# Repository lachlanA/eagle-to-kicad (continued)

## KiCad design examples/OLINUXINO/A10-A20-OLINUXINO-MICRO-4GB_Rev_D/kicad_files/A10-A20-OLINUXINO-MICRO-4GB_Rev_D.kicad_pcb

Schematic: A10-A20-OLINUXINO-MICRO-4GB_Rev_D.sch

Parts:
1.2V_CPU233, 1.2V_INT233, 1.5V233, 2.5V233, 3.0VA233, 3.3V233, 5VEXT233: TESTPADTESTPAD_40-ROUND; GOGO_TESTPAD_40-ROUND
5V_E233: Open; JUMPER_SJ_1_SMALLER
5V_E_SATA233: JUMPER_SJ_1_SMALLER
5V_PWR233: NA(DW02S); PENKO_DW02S
5V_SATA_PWR233: DW02S; PENKO_DW02S
+5V233: TESTPADTESTPAD_40-ROUND; GOGO_TESTPAD_40-ROUND
BAT233: TESTPADTESTPAD_40-ROUND; GOGO_TESTPAD_40-ROUND
C1, C4, C6, C8, C9, C12, C16, C17, C20, C28, C29, C30, C31, C32, C33, C34, C35, C36, C37, C38, C39, C40, C41, C42, C43, C44, C45, C46, C47, C48, C49, C50, C51, C52, C53, C54, C55, C58, C81, C111, C114, C117, C118, C119, C120, C224, C225, C226, C227, C228, C229, C230, C231, C232: 220nF; RCL_C0603_DWS
C2, C3, C5, C7, C10, C11, C14, C15, C18, C19, C21, C22, C23, C24, C25, C26, C27, C57, C59, C60, C61, C62, C68, C69, C70, C77, C78, C79, C80, C82, C83, C84, C85, C86, C87, C106, C134, C139, C155, C169, C175, C184, C189, C191: 220nF; RCL_C0402_TI
C13, C56, C64, C67, C76, C101, C103, C104, C105, C109, C115, C133, C138, C157, C168, C173, C186, C190, C193, C194, C197, C198, C199, C204, C205, C206, C207, C209, C210, C211, C212, C219, C220: 22uF/6.3V; RCL_C0603_DWS
C63, C65, C66, C74, C75, C88, C89, C90, C92, C93, C94, C95, C96, C122, C124, C125, C130, C137, C161, C170, C171, C176, C203, C216, C221: 100nF; RCL_C0603_DWS
C71, C181, C183, C185, C188: NA; RCL_C0603_DWS
C72, C73, C99, C100: 33pF; RCL_C0603_DWS
C91, C110, C146, C150, C167, C174: 1uF; RCL_C0603_DWS
C97, C98: 10pF; RCL_C0603_DWS
C102: 100nF; RCL_C0402_TI
C107, C108: NC; RCL_C0402_TI
C112, C113, C121, C128, C136, C145, C147, C148, C149, C151, C152, C156, C158, C159, C162, C164, C166, C172, C177, C178, C179, C180, C187: 10uF/6.3V; RCL_C0603_DWS
C116, C144: NA(2.2uF); RCL_C0603_DWS
C123, C126, C135: 100uF/16V/LOWESR/105C/6.3x11mm_RM2.5; RCL_E2_5-6_3
C127, C129, C131, C132, C160, C165, C182, C218: 1nF; RCL_C0603_DWS
C140, C141, C142, C143, C200: 10nF; RCL_C0402_TI
C153, C154: NA; RCL_C0402_TI
C163, C201: 3.3nF; RCL_C0603_DWS
C192, C196: 470nF; RCL_C0603_DWS
C195, C208: 22pF; RCL_C0603_DWS
C202: 470uF/25V/LOWESR/105C; RCL_E5-10_5
C213, C214, C215: NA(22uF/6.3V); RCL_C0603_DWS
CHGLED233: LED/YELLOW/0603; DOUBLE-SIDE_LED-0603
D1, D3: 1N5819(S4SOD-123); GOGO_SOD-123
D4: 1N5822/SS34/SMA; GOGO_MLL-41
D5: SMBJ16A; OLIMEX_DISCRET_DO214AA
D6: 1N5822/SS34/SMA; SEMICON-SMD-IPC_MELF-MLL41
ENTER233: SIDE_WTCM-TR(3X4); GOGO_SW_TAKT3X4
ESC233: SIDE_WTCM-TR(3X4); GOGO_SW_TAKT3X4
FET1, FET4: IRLML6402; PENKO_SOT23
FET2, FET3: BSS138; PENKO_SOT23
FUSE1: FSMD035; GOGO_1206
GND233: TESTPADTESTPAD_40-ROUND; GOGO_TESTPAD_40-ROUND
GND_PIN233: TESTPAD3; GOGO_TEST_PAD40_70_SQUARE
GPIO-1, GPIO-2, GPIO-3: GBH-254-SMT-40; CON-HARTING-ML_ML40-MALE(GBH-254-SMT-40)
HDMI233: HDMI-SWM-19; OLIMEX_CONNECTORS_HDMI-SWM-19
HEADPHONES233: PJ-W47S-05D2-LF_V2; GOGO_PJ-W47S-05D2-LF_5PIN_V2
HOME233: SIDE_WTCM-TR(3X4); GOGO_SW_TAKT3X4
IPSOUT233: TESTPADTESTPAD_40-ROUND; GOGO_TESTPAD_40-ROUND
L1, L2, L3, L7, L15, L16, L17: FB0805/600R/200mA(201209-601); RCL_L0805_5MIL_DWS
L4, L5: CL470nH/0805/1.76R/250mA; RCL_L0805_5MIL_DWS
L6, L8, L10, L11: FB0805/600R/2A; RCL_L0805_5MIL_DWS
L12, L13, L14, L18, L20, L21: 2.2uH/1.5A/DCR<0.1R/CD32; OLIMEX_DISCRET_CD32
L19: 10uH/3.15A/20%; OLIMEX_DISCRET_8X8MM_3131
LAN233: RJLBC-060TC1_GND_MILLING; OLIMEX_CONNECTORS_RJLBC-060TC1_MILLING
LCD_CON233: GBH-254-SMT-40; CON-HARTING-ML_ML40-MALE(GBH-254-SMT-40)
LED1: LED/GREEN/0603; DOUBLE-SIDE_LED-0603
LIPO_BAT233: DW02R; PENKO_DW02R
MENU233: SIDE_WTCM-TR(3X4); GOGO_SW_TAKT3X4
MIC2: NA(HN1x2); JUMPER_JP1
MIC_IN233: PJ-W47S-05D2-LF_V2; GOGO_PJ-W47S-05D2-LF_5PIN_V2
NAND_E233: Close; JUMPER_SJ_1_SMALLER_CLOSE_10MILS
ODT1: TESTPADTESTPAD_40-ROUND; GOGO_TESTPAD_40-ROUND
PWR233: YDJ-1136; GOGO_PWR_JACK_UNI_MILLING
PWR_BUT233: SIDE_WTCM-TR(3X4); GOGO_SW_TAKT3X4
PWR_LED233: LED/RED/0603; DOUBLE-SIDE_LED-0603
Q1: 4SB25.000F20E15/5x3.2mm/20ppm/20pF; CRYSTAL_HCX-4S
Q2: 32768Hz/6pF; CRYSTAL_TC26H_3_REPAIR_SMD
Q3: 4SB24.000F20E15/5x3.2mm/20ppm/20pF; CRYSTAL_HCX-4S
R1, R2, R4, R6, R8, R20, R37, R39, R57: 2k/1%; RCL_R0603_5MIL_DWS
R3, R31, R51, R53, R60, R62, R63, R66, R68, R71, R72, R74: 1R; RCL_R0603_5MIL_DWS
R5, R23, R25, R49, R50: NA; RCL_R0603_5MIL_DWS
R7, R9, R16: 237R/1%; RCL_R0603_5MIL_DWS
R10, R18, R19, R21, R30, R33, R38, R44, R46, R47, R54, R105, R136, R137: 10k; RCL_R0603_5MIL_DWS
R11, R17, R29, R91: 100k/1%; RCL_R0603_5MIL_DWS
R12, R15: NA; RCL_R0402_TI
R13, R14: NA(2.2k); RCL_R0603_5MIL_DWS
R22, R26: 560R; RCL_R0603_5MIL_DWS
R24, R34, R69, R87: 0R(Board_Mounted); OLIMEX_DISCRET_0603_0R
R27, R28, R40, R52, R79, R84, R95: 47k; RCL_R0603_5MIL_DWS
R32, R65, R70, R73, R75, R76, R81, R82, R83, R85, R93, R94, R120: 2.2k; RCL_R0603_5MIL_DWS
R35: NA(0R); RCL_R0603_5MIL_DWS
R36, R56, R67: 200k/1%; RCL_R0603_5MIL_DWS
R41, R86, R104: 1k/1%; RCL_R0603_5MIL_DWS
R42, R61, R77, R80, R89, R138: 4.99k/1%; RCL_R0603_5MIL_DWS
R43, R103: 51R; RCL_R0603_5MIL_DWS
R45, R48, R55, R100: 13k/1%; RCL_R0603_5MIL_DWS
R58: 100R; RCL_R0603_5MIL_DWS
R59: 0.03R/1%; RCL_R1206_5MIL_WS
R64: 191R/1%; RCL_R0603_5MIL_DWS
R78: 3.32k/1%; RCL_R0603_5MIL_DWS
R88, R97: 8.25k/1%; RCL_R0603_5MIL_DWS
R90, R92: 1.1k/1%; RCL_R0603_5MIL_DWS
R96: 6.81k/1%; RCL_R0603_5MIL_DWS
R98: 10k/1%; RCL_R0603_5MIL_DWS
R99: 11k/1%; RCL_R0603_5MIL_DWS
R101: 16.2k/1%; RCL_R0603_5MIL_DWS
R102: 22.1k/1%; RCL_R0603_5MIL_DWS
R106, R107, R108, R109, R110, R111, R112, R113, R114, R115, R116, R117, R118, R119, R133, R134, R135: 22R; RCL_R0402_TI
R121: NA(10k); RCL_R0603_5MIL_DWS
R122, R123, R124, R125, R126, R127, R128, R129, R130, R131, R132: NA(0R); RCL_R0402_TI
RECOVERY233: SIDE_WTCM-TR(3X4); GOGO_SW_TAKT3X4
RESET233: SIDE_WTCM-TR(3X4); GOGO_SW_TAKT3X4
RM1, RM2, RM3, RM4, RM5, RM6, RM7, RM8, RM16, RM17, RM18, RM19, RM20, RM21: RA0805_(4X0402)_22R; OLIMEX_DISCRET_R_MATRIX_4_0402_25X625
RM9, RM10: RA1206_(4X0603)_4B8_4.7k; OLIMEX_DISCRET_R_MATRIX_4
RM13: RA1206_(4X0603)_4B8_51R; OLIMEX_DISCRET_R_MATRIX_4
RM14, RM15: RA1206_(4X0603)_4B8_100K; OLIMEX_DISCRET_R_MATRIX_4
RM24: RA1206_(4X0603)_4B8_75R; OLIMEX_DISCRET_R_MATRIX_4
RM25: RA1206_(4X0603)_4B8_10k; OLIMEX_DISCRET_R_MATRIX_4
SATA233: SATA-PWA-07; OLIMEX_CONNECTORS_SATA-PWA-07
SCKE1: TESTPADTESTPAD_40-ROUND; GOGO_TESTPAD_40-ROUND
SD/MMC1: MICRO_SD/MMC_CP_NEWTFC-WPAPR-08; OLIMEX_CONNECTORS_TFC-WPAPR-08
SD/MMC2: PSD006A-LT2-BA0; OLIMEX_CONNECTORS_SD_CARD
SEARCH233: SIDE_WTCM-TR(3X4); GOGO_SW_TAKT3X4
T1: BC846B; SEMICON-SMD-IPC_SOT23
U1: A10/A20; OLIMEX_IC_TFBGA441
U2, U3: H5TQ2G63BFR_MEM4G16D3EABG-125; OLIMEX_IC_FBGA96_MEM
U6: AT24C16BN-SH; GOGO_SO-08MN
U7: RTL8201CP; OLIMEX_IC_LQFP48
U8: H27UBG8T2BTR; OLIMEX_IC_TSOP48
U9, U10, U11: SY6280; OLIMEX_IC_SOT23-5
U12: AXP209(QFN48); OLIMEX_IC_QFN48
U13, U15: SY8008C(AA)C; OLIMEX_IC_SOT23-5
U14: MP1482DS; OLIMEX_IC_SOIC8
U16: SY7208(SOT23-6); OLIMEX_IC_SOT23-6
U17, U22, U23: RCLAMP0524P; OLIMEX_IC_SLP2510P8
UART0: HN1X4; PENKO_HN1X4
UEXT1, UEXT2: GBH-254-SMT-10; CON-HARTING-ML_ML10_S
USB_HOST233: USB_TWO_LEVEL; OLIMEX_CONNECTORS_USB_TWO_LEVEL
USB_OTG233: USB-OTG; OLIMEX_CONNECTORS_USB_MINI_9PIN
VGA233: WU06S; DOUBLE-SIDE_CON1.27MM-6-SMALL_ICSP
VOL+233: SIDE_WTCM-TR(3X4); GOGO_SW_TAKT3X4
VOL-233: SIDE_WTCM-TR(3X4); GOGO_SW_TAKT3X4
VPS+233: Open; JUMPER_SJ_1_SMALLER
VPS-233: Open; JUMPER_SJ_1_SMALLER
VP_0, VP_1, VP_2, VP_3, VP_4, VP_5, VP_6, VP_7, VP_9, VP_10, VP_11, VP_12, VP_13, VP_14, VP_15, VP_16, VP_18, VP_19, VP_20, VP_21, VP_22, VP_23, VP_24, VP_25, VP_27, VP_28, VP_29, VP_30, VP_31, VP_32, VP_33, VP_34, VP_36, VP_37, VP_38, VP_39, VP_40, VP_41, VP_42, VP_44, VP_45, VP_46, VP_47, VP_48, VP_49, VP_54, VP_55, VP_56: VPDEV0; VPAD_VPAC0
VP_8, VP_17, VP_26, VP_35: VPDEV1; VPAD_VPAC1
VP_43: VPDEV2; VPAD_VPAC2
VP_50, VP_51, VP_53: VPDEV3; VPAD_VPAC3
VP_52: VPDEV4; VPAD_VPAC4
VR1: AP1231-2.5V(SOT23-5); OLIMEX_DISCRET_SOT-23-5

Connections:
+5V: 5V_E233.2, 5V_E_SATA233.1, 5V_PWR233.1, +5V233.1, C125.1, C128.1, C136.1, C214.2, C215.2, D4.K (C), FET1.2 (S), FET4.2 (S), FUSE1.1, GPIO-1.1, GPIO-2.1, GPIO-3.1, LCD_CON233.1, R37.2, R39.2, R41.1, R104.1, R137.1, U9.5 (IN), U10.5 (IN), U11.5 (IN)
+5V_OTG_PWR: C124.1, L6.1, R17.1, R63.2, U12.31 (VBUS), USB_OTG233.VBUS
+15V: 5VEXT233.1, 5V_E233.1, C204.1, C205.1, D4.A, FET1.1 (G), L19.2, R62.2, R80.2, R81.1, U12.32 (ACIN), U12.33 (ACIN)
+24V: BAT233.1, C150.2, C152.1, C209.2, LIPO_BAT233.1, R59.2, U12.38 (BAT), U12.39 (BAT), U12.42 (BATSENSE)
ADBG: U1.N8 (ADBG)
BA0: RM21.1.2 (2), U2.M2 (BA0), U3.M2 (BA0)
BA1: RM21.4.2 (2), U2.N8 (BA1), U3.N8 (BA1)
BA2: RM21.2.2 (2), U2.M3 (BA2), U3.M3 (BA2)
CASN: RM18.3.2 (2), U2.K3 (#CAS), U3.K3 (#CAS)
CKE: RM20.3.2 (2), U2.K9 (CKE), U3.K9 (CKE)
CLK: R118.1, U2.J7 (CK), U3.J7 (CK)
CLKN: R119.1, U2.K7 (#CK), U3.K7 (#CK)
CPU-REF: C1.2, C12.2, C71.2, R1.1, R2.2, R5.2, U1.AA8 (SVREF3), U1.H3 (SVREF0), U1.H4 (SVREF1), U1.Y5 (SVREF2)
DDR3_ODT: R15.1, U2.K1 (ODT), U3.K1 (ODT)
DDR3_RST: R4.1, R12.1, U2.T2 (#RESET), U3.T2 (#RESET)
DDR3_SA0: RM17.4.1 (1), U1.W4 (SA0)
DDR3_SA1: RM19.4.1 (1), U1.R4 (SA1)
DDR3_SA2: RM18.4.1 (1), U1.U4 (SA2)
DDR3_SA3: RM20.2.1 (1), U1.M4 (SA3)
DDR3_SA4: RM16.2.1 (1), U1.Y4 (SA4)
DDR3_SA5: RM20.4.1 (1), U1.N4 (SA5)
DDR3_SA6: RM17.2.1 (1), U1.V4 (SA6)
DDR3_SA7: RM20.1.1 (1), U1.M3 (SA7)
DDR3_SA8: RM16.3.1 (1), U1.AA3 (SA8)
DDR3_SA9: RM19.2.1 (1), U1.P4 (SA9)
DDR3_SA10: RM21.3.1 (1), U1.L3 (SA10)
DDR3_SA11: RM17.3.1 (1), U1.W3 (SA11)
DDR3_SA12: RM19.1.1 (1), U1.P3 (SA12)
DDR3_SA13: RM16.1.1 (1), U1.Y3 (SA13)
DDR3_SA14: RM19.3.1 (1), U1.R3 (SA14)
DDR3_SA15: RM16.4.1 (1), U1.AA4 (SCS1)
DDR3_SBA0: RM21.1.1 (1), U1.K3 (SBA0)
DDR3_SBA1: RM21.4.1 (1), U1.L4 (SBA1)
DDR3_SBA2: RM21.2.1 (1), U1.K4 (SBA2)
DDR3_SCAS: RM18.3.1 (1), U1.U3 (SCAS)
DDR3_SCS0: RM17.1.1 (1), U1.V3 (SCS0)
DDR3_SDQM0: R110.2, U1.AC6 (SDQM0)
DDR3_SDQM1: R111.2, U1.W1 (SDQM1)
DDR3_SDQM2: R112.2, U1.R2 (SDQM2)
DDR3_SDQM3: R113.2, U1.G1 (SDQM3)
DDR3_SDQS0: R106.2, U1.AB6 (SDQS0)
DDR3_SDQS0#: R107.2, U1.AC5 (SDQS0#)
DDR3_SDQS1: R108.2, U1.AB1 (SDQS1)
DDR3_SDQS1#: R109.2, U1.AA2 (SDQS1#)
DDR3_SDQS2: R114.2, U1.R1 (SDQS2)
DDR3_SDQS2#: R115.2, U1.P2 (SDQS2#)
DDR3_SDQS3: R116.2, U1.K1 (SDQS3)
DDR3_SDQS3#: R117.2, U1.J2 (SDQS3#)
DDR3_SRAS: RM18.2.1 (1), U1.T4 (SRAS)
DDR3_SWE: RM18.1.1 (1), U1.T3 (SWE)
DDR_VREF: C17.2, C35.2, R5.1, R6.1, R8.2, U2.H1 (VREFDQ), U2.M8 (VREFCA), U3.H1 (VREFDQ), U3.M8 (VREFCA)
DQ0: RM1.2.1 (1), U2.E3 (DQL0)
DQ1: RM2.2.1 (1), U2.F7 (DQL1)
DQ2: RM1.3.1 (1), U2.F2 (DQL2)
DQ3: RM2.3.1 (1), U2.F8 (DQL3)
DQ4: RM2.4.1 (1), U2.H3 (DQL4)
DQ5: RM1.4.1 (1), U2.H8 (DQL5)
DQ6: RM2.1.1 (1), U2.G2 (DQL6)
DQ7: RM1.1.1 (1), U2.H7 (DQL7)
DQ8: RM3.2.1 (1), U2.D7 (DQU0)
DQ9: RM4.2.1 (1), U2.C3 (DQU1)
DQ10: RM3.3.1 (1), U2.C8 (DQU2)
DQ11: RM4.3.1 (1), U2.C2 (DQU3)
DQ12: RM4.4.1 (1), U2.A7 (DQU4)
DQ13: RM3.4.1 (1), U2.A2 (DQU5)
DQ14: RM4.1.1 (1), U2.B8 (DQU6)
DQ15: RM3.1.1 (1), U2.A3 (DQU7)
DQ16: RM5.2.1 (1), U3.E3 (DQL0)
DQ17: RM6.2.1 (1), U3.F7 (DQL1)
DQ18: RM5.3.1 (1), U3.F2 (DQL2)
DQ19: RM6.3.1 (1), U3.F8 (DQL3)
DQ20: RM6.4.1 (1), U3.H3 (DQL4)
DQ21: RM5.4.1 (1), U3.H8 (DQL5)
DQ22: RM6.1.1 (1), U3.G2 (DQL6)
DQ23: RM5.1.1 (1), U3.H7 (DQL7)
DQ24: RM7.2.1 (1), U3.D7 (DQU0)
DQ25: RM8.2.1 (1), U3.C3 (DQU1)
DQ26: RM7.3.1 (1), U3.C8 (DQU2)
DQ27: RM8.3.1 (1), U3.C2 (DQU3)
DQ28: RM8.4.1 (1), U3.A7 (DQU4)
DQ29: RM7.4.1 (1), U3.A2 (DQU5)
DQ30: RM8.1.1 (1), U3.B8 (DQU6)
DQ31: RM7.1.1 (1), U3.A3 (DQU7)
ECOL: U1.D13 (ECOL/CAN_TX/UART1_DCD/PA16), U7.1 (COL)
ECRS: U1.E12 (ECRS/UART7_RX/UART1_DSR/PA15), U7.23 (CRS)
EMDC: U1.E10 (EMDC/UART1_RX/PA11), U7.25 (MDC)
EMDIO: RM10.1.1 (1), U1.D11 (EMDIO/UART6_TX/UART1_RTS/PA12), U7.26 (MDIO)
ENTER_BUT: ENTER233.1_1 (1), GPIO-1.18, R102.2
EPHY-RST#: R25.1, U1.C13 (ETXERR/CAN_RX/UART1_RING/PA17)
ERXCK: U1.D9 (ERXCK/SPI3_MISO/PA8), U7.16 (RXC)
ERXD0: U1.E6 (ERXD0/SPI1_MISO/PA3), U7.21 (RXD0)
ERXD1: U1.D6 (ERXD1/SPI1_MOSI/PA2), U7.20 (RXD1)
ERXD2: U1.E5 (ERXD2/SPI1_CLK/PA1), U7.19 (RXD2)
ERXD3: U1.D5 (ERXD3/SPI1_CS0//PA0), U7.18 (RXD3)
ERXDV: U1.D10 (ERXDV/UART1_TX/PA10), U7.22 (RXDV)
ERXERR: U1.E9 (ERXERR/SPI3_CS1/PA9), U7.24 (RXER/FXEN)
ESC_BUT: ESC233.1_1 (1), GPIO-1.16, R101.2, R102.1
ETXCK: U1.D12 (ETXCK/UART7_TX/UART1_DTR/PA14), U7.7 (TXC)
ETXD0: U1.E8 (ETXD0/SPI3_MOSI/PA7), U7.6 (TXD0)
ETXD1: U1.D8 (ETXD1/SPI3_CLK/PA6), U7.5 (TXD1)
ETXD2: U1.E7 (ETXD2/SPI3_CS0/PA5), U7.4 (TXD2)
ETXD3: U1.D7 (ETXD3/SPI1_CS1/PA4), U7.3 (TXD3)
ETXEN: U1.E11 (ETXEN/UART6_RX/UART1_CTS/PA13), U7.2 (TXEN)
EXTEN: U12.20 (EXTEN), U15.1 (EN), U16.4 (EN)
FMINL: GPIO-1.36, U1.Y20 (FMINL)
FMINR: GPIO-1.34, U1.Y21 (FMINR)
GPIO1: GPIO-2.35, R17.2, R56.1, U12.18 (GPIO1)
GPIO2: GPIO-2.37, U12.5 (GPIO2)
GPIO3: GPIO-2.39, U12.3 (GPIO3)
HCEC: HDMI233.13, U1.P23 (CEC_HDMI), U23.1 (IN1), U23.10 (OUT1)
HDMI_5V_SOURCE: FUSE1.2, HDMI233.18
HHPD: HDMI233.19, R40.1, U1.P22 (HPD_HDMI), U23.5 (IN4), U23.6 (OUT4)
HOME_BUT: GPIO-1.14, HOME233.1_1 (1), R100.2, R101.1
HPCOM: L17.1, R135.2, U1.AA19 (HPCOM), U1.AA20 (HPCOMFB)
HPOUTL: L16.1, R134.2, U1.Y19 (HPOUTL)
HPOUTR: L15.1, R133.2, U1.W19 (HPOUTR)
HSCL: HDMI233.15, R37.1, U1.R23 (SCL_HDMI), U23.2 (IN2), U23.9 (OUT2)
HSDA: HDMI233.16, R39.1, U1.R22 (SDA_HDMI), U23.4 (IN3), U23.7 (OUT3)
HTX0N: HDMI233.9, U1.V22 (TX0N_HDMI), U22.2 (IN2), U22.9 (OUT2)
HTX0P: HDMI233.7, U1.V23 (TX0P_HDMI), U22.1 (IN1), U22.10 (OUT1)
HTX1N: HDMI233.6, U1.U22 (TX1N_HDMI), U17.5 (IN4), U17.6 (OUT4)
HTX1P: HDMI233.4, U1.U23 (TX1P_HDMI), U17.4 (IN3), U17.7 (OUT3)
HTX2N: HDMI233.3, U1.T22 (TX2N_HDMI), U17.2 (IN2), U17.9 (OUT2)
HTX2P: HDMI233.1, U1.T23 (TX2P_HDMI), U17.1 (IN1), U17.10 (OUT1)
HTXCN: HDMI233.12, U1.W22 (TXCN_HDMI), U22.5 (IN4), U22.6 (OUT4)
HTXCP: HDMI233.10, U1.W23 (TXCP_HDMI), U22.4 (IN3), U22.7 (OUT3)
IPSOUT: C145.2, C156.1, C162.1, C166.1, C177.2, C180.1, C194.1, C207.1, C210.2, CHGLED233.A, IPSOUT233.1, L20.1, RESET233.1_1 (1), U12.7 (VIN2), U12.13 (LDO24IN), U12.14 (VIN3), U12.21 (APS), U12.34 (IPSOUT), U12.35 (IPSOUT), U12.40 (LDO3IN), U12.44 (VIN1), U13.4 (IN), U15.4 (IN), U16.5 (IN)
LCD_CLK: LCD_CON233.31, U1.Y9 (LCD0_CLK/SMC_VCCEN/PD24)
LCD_D0: LCD_CON233.21, U1.AB15 (LCD0_D0/LVDS0_VP0/PD0)
LCD_D1: LCD_CON233.22, U1.AC15 (LCD0_D1/LVDS0_VN0/PD1)
LCD_D2: LCD_CON233.23, U1.AB14 (LCD0_D2/LVDS0_VP1/PD2)
LCD_D3: LCD_CON233.24, U1.AC14 (LCD0_D3/LVDS0_VN1/PD3)
LCD_D4: LCD_CON233.25, U1.AB13 (LCD0_D4/LVDS0_VP2/PD4)
LCD_D5: LCD_CON233.26, U1.AC13 (LCD0_D5/LVDS0_VN2/PD5)
LCD_D6: LCD_CON233.27, U1.AB12 (LCD0_D6/LVDS0_VPC/PD6)
LCD_D7: LCD_CON233.28, U1.AC12 (LCD0_D7/LVDS0_VNC/PD7)
LCD_D8: LCD_CON233.13, U1.AB11 (LCD0_D8/LVDS0_VP3/PD8)
LCD_D9: LCD_CON233.14, U1.AC11 (LCD0_D9/LVDS0_VN3/PD9)
LCD_D10: LCD_CON233.15, U1.Y15 (LCD0_D10/LVDS1_VP0/PD10)
LCD_D11: LCD_CON233.16, U1.AA15 (LCD0_D11/LVDS1_VN0/PD11)
LCD_D12: LCD_CON233.17, U1.Y14 (LCD0_D12/LVDS1_VP1/PD12)
LCD_D13: LCD_CON233.18, U1.AA14 (LCD0_D13/LVDS1_VN1/PD13)
LCD_D14: LCD_CON233.19, U1.Y13 (LCD0_D14/LVDS1_VP2/PD14)
LCD_D15: LCD_CON233.20, U1.AA13 (LCD0_D15/LVDS1_VN2/PD15)
LCD_D16: LCD_CON233.5, U1.Y12 (LCD0_D16/LVDS1_VPC/PD16)
LCD_D17: LCD_CON233.6, U1.AA12 (LCD0_D17/LVDS1_VNC/PD17)
LCD_D18: LCD_CON233.7, U1.Y11 (LCD0_D18/LVDS1_VP3/PD18)
LCD_D19: LCD_CON233.8, U1.AA11 (LCD0_D19/LVDS1_VN3/PD19)
LCD_D20: LCD_CON233.9, U1.Y10 (LCD0_D20/CSI1_MCLK/PD20)
LCD_D21: LCD_CON233.10, U1.AA10 (LCD0_D21/SMC_VPPEN/PD21)
LCD_D22: LCD_CON233.11, U1.AB10 (LCD0_D22/SMC_VPPPP/PD22)
LCD_D23: LCD_CON233.12, U1.AC10 (LCD0_D23/SMC_DET/PD23)
LCD_DE: LCD_CON233.32, U1.AA9 (LCD0_DE/SMC_RST/PD25)
LCD_HSYNC: LCD_CON233.29, R103.1, U1.AB9 (LCD0_HSYNC/SMC_SLK/PD26)
LCD_PWR: LCD_CON233.35, U1.C4 (LCD1_D8/ATAD4/KP_IN0/MS_D0/EINT8/CSI1_D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)
LCD_VSYNC: LCD_CON233.30, R43.1, U1.AC9 (LCD0_VSYNC/SMC_SDA/PD27)
LDO3_2.8V: C86.2, C179.1, U1.F19 (VCC_CSI0), U12.41 (LDO3)
LDO4_2.8V: C87.2, C187.1, U1.E18 (VCC_CSI1), U12.11 (LDO4)
LINEINL: GPIO-1.32, U1.AB20 (LINEINL)
LINEINR: GPIO-1.30, U1.AB21 (LINEINR)
LRADC0: C218.1, R91.2, R96.1, U1.AB23 (LRADC0)
LRADC1: GPIO-1.39, U1.AB22 (LRADC1)
MENU_BUT: GPIO-1.10, MENU233.1_1 (1), R98.2, R99.1
MIC1OUTN: GPIO-1.40, U1.AC23 (MIC1OUTN)
MIC1OUTP: GPIO-1.38, U1.AC22 (MIC1OUTP)
MICIN1: C161.2, U1.AC20 (MICIN1)
MICIN2: MIC2.1, U1.AC21 (MICIN2)
MICM: C110.1, C147.1, C148.1, R34.2 (1.2)
unnamed: C120.2, C121.2, U1.AC19 (HPVCC)
unnamed: R16.2, U1.AA7 (SZQ)
unnamed: R7.2, U2.L8 (ZQ)
unnamed: R65.2, U12.36 (CHGLED)
unnamed: R9.2, U3.L8 (ZQ)
unnamed: R20.2, U7.28 (RTSET)
unnamed: D3.C, UART0.3
unnamed: L18.1, U13.3 (LX)
unnamed: C146.2, U12.19 (GPIO0/LDO)
unnamed: D1.C, R27.2
unnamed: FET2.1 (G), R43.2
unnamed: R120.1, U12.27 (LDO1SET)
unnamed: RM10.3.1 (1), U7.15 (LED4/PHYAD4)
unnamed: C144.1, U8.26 (NC)
unnamed: C161.1, C163.2, MIC_IN233.2, MIC_IN233.3, R61.2
unnamed: C216.1, R136.1, R138.2, T1.1 (B)
unnamed: FET4.1 (G), R137.2, T1.3 (C)
unnamed: C195.2, R77.2, R78.1, U13.5 (FB)
unnamed: C116.1, R130.2, U8.28 (NC)
unnamed: C63.2, C64.2, L1.1, U7.36 (AVDD33)
unnamed: HEADPHONES233.5, L17.2
unnamed: C206.1, D6.1 (C), FET1.3 (D), R88.2
unnamed: 5V_E_SATA233.2, 5V_SATA_PWR233.1, C197.2, C213.2, FET4.3 (D)
unnamed: HEADPHONES233.2, L16.2
unnamed: HEADPHONES233.3, L15.2
unnamed: FET3.1 (G), R103.2
unnamed: C178.1, R69.2 (1.2), U12.12 (LDO2)
unnamed: C202.+, D5.C, PWR233.+, R79.1, U14.2 (IN)
unnamed: C92.2, R25.2, RM10.2.1 (1), U7.42 (RESETB)
unnamed: C96.2, RM13.1.1 (1), RM13.2.1 (1)
unnamed: C171.2, R134.1
unnamed: C176.2, R135.1
unnamed: C203.1, U14.8 (SS)
unnamed: R79.2, U14.7 (EN)
unnamed: PWR_BUT233.1_1 (1), R70.1
unnamed: LAN233.1 (TD+), RM13.4.2 (2), U7.34 (TPTX+)
unnamed: LAN233.2 (TD-), RM13.3.2 (2), U7.33 (TPTX-)
unnamed: LAN233.7 (RD+), RM13.2.2 (2), U7.31 (TPRX+)
unnamed: C192.2, U1.AA16 (VRP_TVIN)
unnamed: CHGLED233.C, R65.1
unnamed: C170.2, R133.1
unnamed: LAN233.8 (RD-), RM13.1.2 (2), U7.30 (TPRX-)
unnamed: C200.1, U14.1 (BS)
unnamed: C95.2, RM13.3.1 (1), RM13.4.1 (1)
unnamed: RM9.2.2 (2), U7.10 (LED1/PHYAD1)
unnamed: C200.2, L19.1, U14.3 (SW)
unnamed: RM9.3.2 (2), U7.12 (LED2/PHYAD2)
unnamed: LAN233.KG, R22.1
unnamed: LAN233.AY, RM9.4.2 (2), U7.13 (LED3/PHYAD3)
unnamed: C74.1, L3.1, U7.8 (PWFBIN)
unnamed: C75.1, C76.1, C93.2, L3.2, LAN233.3 (COM), U7.32 (PWFBOUT)
unnamed: LAN233.KY, R26.1
unnamed: R33.1, SD/MMC1.10 (PACK1), SD/MMC1.11 (PACK2), SD/MMC1.12 (PACK3), SD/MMC1.13 (PACK4)
unnamed: C201.1, U14.6 (COMP)
unnamed: C201.2, R85.1
unnamed: R80.1, R86.1, U14.5 (FB)
unnamed: L21.1, U15.3 (LX)
unnamed: C208.2, R89.2, R92.1, U15.5 (FB)
unnamed: C65.2, C66.2, C67.2, L2.1, U7.14 (DVDD33), U7.48 (DVDD33)
unnamed: R22.2, RM9.1.2 (2), U7.9 (LED0/PHYAD0)
unnamed: U8.38 (NC), VPS+233.2, VPS-233.2
unnamed: C155.1, C157.2, R60.2, U1.T13 (VP_HDMI)
unnamed: C153.1, U1.R14 (VREGIO2_HDMI)
unnamed: C154.1, U1.T14 (VREGIO1_HDMI)
unnamed: R23.1, R24.2 (1.2), U1.T9 (EFUSE_VDDQ)
unnamed: C105.2, C106.2, R31.1, U1.P16 (PLLVP25)
unnamed: C97.2, Q2.1, U1.F1 (CLK32K_IN)
unnamed: R45.2, U9.3 (ISET)
unnamed: C123.+, L6.2, R42.2, U9.1 (OUT)
unnamed: R48.2, U10.3 (ISET)
unnamed: C133.2, C134.2, R51.1, U1.L15 (UVCC_T), U1.L16 (UVCC_C)
unnamed: C138.2, C139.2, R53.1, U1.K16 (ULVDD)
unnamed: C140.2, SATA233.2 (A+)
unnamed: C130.1, L8.2, USB_HOST233.1.1
unnamed: C141.2, SATA233.3 (A-)
unnamed: C142.2, SATA233.5 (B-)
unnamed: C143.2, SATA233.6 (B+)
unnamed: C107.2, U1.T16 (PLLDV)
unnamed: C98.2, Q2.2, U1.F2 (CLK32K_OUT)
unnamed: R64.2, U1.V21 (REXT_SATA)
unnamed: R67.2, U12.23 (BIAS)
unnamed: C108.2, U1.R15 (PLLVREG)
unnamed: C113.2, C114.2, U1.W21 (VRP)
unnamed: D6.2 (A), L20.2, U16.1 (LX)
unnamed: C88.2, R21.2, U8.19 (#WP)
unnamed: R58.2, U12.37 (TS)
unnamed: R88.1, R90.1, U16.3 (FB)
unnamed: L12.1, U12.45 (LX1)
unnamed: C150.1, C151.1, L12.2, R59.1, U12.43 (CHSENSE)
unnamed: PWR_LED233.A, R81.2
unnamed: L13.1, U12.8 (LX2)
unnamed: L14.1, U12.15 (LX3)
unnamed: C174.2, U12.24 (VREF)
unnamed: C110.2, U1.W20 (VRA1)
unnamed: C149.2, R62.1
unnamed: C158.2, R63.1
unnamed: R55.2, U11.3 (ISET)
unnamed: C182.2, R70.2, U12.47 (PWRON)
unnamed: R73.2, RESET233.2_1 (0), U12.4 (N_OE)
unnamed: R38.1, SD/MMC2.CD (CP)
unnamed: C111.2, C112.2, R36.1, U1.V20 (VRA2)
unnamed: C147.2, R57.1, R61.1
unnamed: R35.1, U1.T10 (JTAG_SEL)
unnamed: C168.2, C169.2, R66.1, U1.N15 (VDD25_SATA), U1.N16 (VDD25_SATA)
unnamed: C126.+, L8.1, U10.1 (OUT)
unnamed: L11.2, USB_HOST233.GND1, USB_HOST233.GND2, USB_HOST233.GND3, USB_HOST233.GND4
unnamed: C137.1, L10.2, USB_HOST233.2.1
unnamed: C135.+, L10.1, U11.1 (OUT)
unnamed: C173.2, C175.2, R68.1, U1.M15 (VDD12_SATA), U1.M16 (VDD12_SATA)
unnamed: C13.2, C14.2, C15.2, C16.2, R3.1, U1.M8 (VDD_DLL), U1.N9 (VDD_DLL), U1.P9 (VDD_DLL)
unnamed: C191.1, C193.2, R74.2, U1.W16 (VCC33_TVIN)
unnamed: C189.1, C190.2, R72.2, U1.W15 (VCC33_TVOUT)
unnamed: C184.1, C186.2, R71.2, U1.W17 (VDD25_TVIN)
unnamed: C196.2, U1.Y16 (VRN_TVIN)
unnamed: LCD_CON233.33, R49.1
unnamed: LCD_CON233.34, R50.1
unnamed: LED1.A, R32.2
unnamed: NAND_E233.1, R19.2, U8.9 (#CE)
unnamed: L7.2, USB_OTG233.GND1, USB_OTG233.GND2, USB_OTG233.GND3, USB_OTG233.GND4
NALE: U1.M22 (NALE/SPI0_MISO/PC1), U8.17 (ALE)
NAND_DQS: R129.2, U8.35 (NC)
NCE0: NAND_E233.2, U1.K23 (NCE0/PC4)
NCLE: U1.L23 (NCLE/SPI0_CLK/PC2), U8.16 (CLE)
NDQ0: R122.1, U1.H23 (NDQ0/SDC2_D0/PC8), U8.29 (I/O0)
NDQ1: R123.1, U1.H22 (NDQ1/SDC2_D1/PC9), U8.30 (I/O1)
NDQ2: R124.1, U1.G23 (NDQ2/SDC2_D2/PC10), U8.31 (I/O2)
NDQ3: R126.1, U1.G22 (NDQ3/SDC2_D3/PC11), U8.32 (I/O3)
NDQ4: U1.H21 (NDQ4/PC12), U8.41 (I/O4)
NDQ5: U1.H20 (NDQ5/PC13), U8.42 (I/O5)
NDQ6: U1.G21 (NDQ6/PC14), U8.43 (I/O6)
NDQ7: U1.G20 (NDQ7/PC15), U8.44 (I/O7)
NMI_N: GPIO-2.38, R27.1, U1.F5 (NMI#), U12.48 (IRQ/WAKEUP)
NRB0: R18.2, R128.1, R131.2, U1.J23 (NRB0/SDC2_CMD/PC6), U8.7 (R/#B)
NRBO/NRB1: R131.1, R132.1, U8.6 (NC)
NRE: U1.K22 (NRE#/PC5), U8.8 (#RE)
NWE: U1.M23 (NWE#/SPI0_MOSI/PC0), U8.18 (#WE)
ODT0: R15.2, U1.AA5 (ODT0)
ODT1: ODT1.1, U1.J3 (ODT1)
PB2/PWM0: LCD_CON233.36, U1.A14 (PWM0/PB2)
PB3: GPIO-3.6, R49.2, U1.B14 (IR0_TX/SPDIF_MCLK/STANBYWFI/PB3)
PB4: GPIO-3.8, R50.2, U1.A13 (IR0_RX/PB4)
PB5: GPIO-3.10, U1.B13 (I2S_MCLK/AC97_MCLK/PB5)
PB6: GPIO-3.12, U1.A12 (I2S_BCLK/AC97_BCLK/PB6)
PB7: GPIO-3.14, U1.B12 (I2S_LRCK/AC97_SYNC/PB7)
PB8/SATA-PWR-EN: GPIO-3.16, R136.2, U1.A11 (I2S_DO0/AC97_DO/PB8)
PB10: GPIO-3.18, U1.C11 (I2S_DO2/PB10)
PB11: GPIO-3.20, U1.C10 (I2S_DO3/PB11)
PB12: GPIO-3.22, U1.C9 (I2S_DI/AC97_DI/SPDIF_DI/PB12)
PB13: GPIO-3.24, U1.B11 (SPI2_CS1/SPDIF_DO/PB13)
PB14: GPIO-3.26, RM25.3.1 (1), U1.A10 (JTAG_MS0/SPI2_CS0/PB14)
PB15: GPIO-3.28, RM25.2.1 (1), U1.B10 (JTAG_CK0/SPI2_CLK/PB15)
PB16: GPIO-3.30, U1.A9 (JTAG_DO0/SPI2_MOSI/PB16)
PB17: GPIO-3.32, RM25.1.1 (1), U1.B9 (JTAG_DI0/SPI2_MISO/PB17)
PC3/NCE1: GPIO-2.21, U1.L22 (NCE1/PC3), U8.10 (NC)
PC7/NRB1: GPIO-2.23, R121.2, R127.1, R132.2, U1.J22 (NRB1/SDC2_CLK/PC7), U8.4 (NC), U8.5 (NC)
PC16: GPIO-2.25, U1.M21 (NWP/PC16)
PC17: GPIO-2.27, U1.F23 (NCE2/PC17)
PC18: GPIO-2.29, U1.F22 (NCE3/PC18)
PC23: GPIO-2.31, U1.G19 (SPI0_CS0/PC23)
PC24/NQS: GPIO-2.33, R129.1, U1.F21 (NDQS/PC24)
PE0: GPIO-2.6, U1.E23 (TS0_CLK/CSI0_PCLK/PE0)
PE1: GPIO-2.8, U1.E22 (TS0_ERR/CSI0_MCLK/PE1)
PE2: GPIO-2.10, U1.D23 (TS0_SYNC/CSI0_HSYNC/PE2)
PE3: GPIO-2.12, U1.D22 (TS0_DVLD/CSI0_VSYNC/PE3)
PE4: GPIO-2.14, U1.C23 (TS0_D0/CSI0_D0/PE4)
PE5: GPIO-2.16, U1.C22 (TS0_D1/CSI0_D1/PE5)
PE6: GPIO-2.18, U1.B23 (TS0_D2/CSI0_D2/PE6)
PE7: GPIO-2.20, U1.B22 (TS0_D3/CSI0_D3/PE7)
PE8: GPIO-2.22, U1.A23 (TS0_D4/CSI0_D4/PE8)
PE9: GPIO-2.24, U1.A22 (TS0_D5/CSI0_D5/PE9)
PE10: GPIO-2.26, U1.B21 (TS0_D6/CSI0_D6/PE10)
PE11: GPIO-2.28, U1.A21 (TS0_D7/CSI0_D7/PE11)
PG0: GPIO-1.5, U1.F20 (TS1_CLK/CSI1_PCLK/SDC1_CMD/PG0)
PG1: GPIO-1.7, U1.E21 (TS1_ERR/CSI1_MLCK/SDC1_CLK/PG1)
PG2: GPIO-1.9, U1.E20 (TS1_SYNC/CSI1_HSYNC/SDC1_D0/PG2)
PG3: GPIO-1.11, U1.D21 (TS1_DVLD/CSI1_VSYNC/SDC1_D1/PG3)
PG4: GPIO-1.13, U1.D20 (TS1_D0/CSI1_D0/SDC1_D2/CSI0_D8/PG4)
PG5: GPIO-1.15, U1.C21 (TS1_D1/CSI1_D1/SDC1_D3/CSI0_D9/PG5)
PG6: GPIO-1.17, U1.E19 (TS1_D2/CSI1_D2/UART3_TX/CSI0_D10/PG6)
PG7: GPIO-1.19, U1.C20 (TS1_D3/CSI1_D3/UART3_RX/CSI0_D11/PG7)
PG8: GPIO-1.21, U1.D19 (TS1_D4/CSI1_D4/UART3_RTS/CSI0_D12/PG8)
PG9: GPIO-1.23, U1.C19 (TS1_D5/CSI1_D5/UART3_CTS/CSI0_D13/PG9)
PG10: GPIO-1.25, U1.D18 (TS1_D6/CSI1_D6/UART4_TX/CSI0_D14/PG10)
PG11: GPIO-1.27, U1.C18 (TS1_D7/CSI1_D7/UART4_RX/CSI0_D15/PG11)
PH0: GPIO-3.5, U1.A6 (LCD1_D0/ATAA0/UART3_TX/EINT0/CSI1_D0/PH0)
PH2/LED: GPIO-3.7, R32.1, U1.C6 (LCD1_D2/ATAA2/UART3_RTS/EINT2/CSI1_D2/P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)
PH7: GPIO-3.9, U1.B4 (LCD1_D7/ATAD3/UART5_RX/MS_CLK/EINT7/CSI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)
PH9: GPIO-3.11, U1.D4 (LCD1_D9/ATAD5/KP_IN1/MS_D1/EINT9/CSI1_D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)
PH10: GPIO-3.13, U1.A3 (LCD1_D10/ATAD6/KP_IN2/MS_D2/EINT10/CSI1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)
PH11/SDC3-DET#: GPIO-3.15, R38.2, RM15.4.1 (1), U1.B3 (LCD1_D11/ATAD7/KP_IN3/MS_D3/EINT11/CSI1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)
PH12: GPIO-3.17, U1.C3 (LCD1_D12/ATAD8/PS2_SCK1/EINT12/CSI1_D12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)
PH13: GPIO-3.19, U1.A2 (LCD1_D13/ATAD9/PS2_SDA1/SMC_RST/EINT13/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)
PH14: GPIO-3.21, U1.B2 (LCD1_D14/ATAD10/KP_IN4/SMC_VPPEN/EINT14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)
PH15: GPIO-3.23, U1.A1 (LCD1_D15/ATAD11/KP_IN5/SMC_VPPPP/EINT15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)
PH16: GPIO-3.25, U1.B1 (LCD1_D16/ATAD12/KP_IN6/SMC_DET/EINT16/C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)
PH17: GPIO-3.27, U1.C1 (LCD1_D17/ATAD13/KP_IN7/SMC_VCCEN/EINT17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)
PH18: GPIO-3.29, U1.C2 (LCD1_D18/ATAD14/KP_OUT0/SMC_SLK/EINT18/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)
PH19: GPIO-3.31, U1.D1 (LCD1_D19/ATAD15/KP_OUT1/SMC_SDA/EINT19/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)
PH20: GPIO-3.33, U1.D2 (LCD1_D20/ATAOE/CAN_TX/EINT20/CSI1_D20/P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)
PH21: GPIO-3.35, U1.D3 (LCD1_D21/ATADREQ/CAN_RX/EINT21/CSI1_D21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)
PH22: GPIO-3.37, U1.E1 (LCD1_D22/ATADACK/KP_OUT2/SDC1_CMD/CSI1_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)
PH23: GPIO-3.39, U1.E2 (LCD1_D23/ATACS0/KP_OUT3/SDC1_CLK/CSI1_D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)
PH24: GPIO-3.34, U1.E3 (LCD1_CLK/ATACS1/KP_OUT4/SDC1_D0/CSI1_PC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)
PH25: GPIO-3.36, U1.E4 (LCD1_DE/ATAIORDY/KP_OUT5/SDC1_D1/CSI1_F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)
PH26: GPIO-3.38, U1.F3 (LCD1_HSYNC/ATAIOR/KP_OUT6/SDC1_D2/CSI1_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)
PH27: GPIO-3.40, U1.F4 (LCD1_VSYNC/ATAIOW/KP_OUT7/SDC1_D3/CSI1_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)
PI0: GPIO-2.9, U1.A20 (GPS_CLK/PI0)
PI1: GPIO-2.11, U1.B20 (GPS_SIGN/PI1)
PI2: GPIO-2.13, U1.A19 (GPS_MAG/PI2)
PI3: GPIO-2.15, U1.B19 (PWM1/PI3)
PI10: GPIO-2.17, U1.C17 (SPI0_CS0/UART5_TX/EINT22/PI10)
PI11: GPIO-2.19, U1.D17 (SPI0_CLK/UART5_RX/EINT23/PI11)
PI14: GPIO-2.30, U1.C15 (PS2_SCK1/TCLKIN0/EINT26/SPI0_CS1/PI14)
PI15: GPIO-2.32, U1.D15 (PS2_SDA1/TCLKIN1/EINT27/SPI1_CS1/PI15)
RASN: RM18.2.2 (2), U2.J3 (#RAS), U3.J3 (#RAS)
RESET_N: C91.2, C94.2, GPIO-2.40, R28.1, U1.C14 (RESET#), U12.25 (PWROK)
SA0: RM17.4.2 (2), U2.N3 (A0), U3.N3 (A0)
SA1: RM19.4.2 (2), U2.P7 (A1), U3.P7 (A1)
SA2: RM18.4.2 (2), U2.P3 (A2), U3.P3 (A2)
SA3: RM20.2.2 (2), U2.N2 (A3), U3.N2 (A3)
SA4: RM16.2.2 (2), U2.P8 (A4), U3.P8 (A4)
SA5: RM20.4.2 (2), U2.P2 (A5), U3.P2 (A5)
SA6: RM17.2.2 (2), U2.R8 (A6), U3.R8 (A6)
SA7: RM20.1.2 (2), U2.R2 (A7), U3.R2 (A7)
SA8: RM16.3.2 (2), U2.T8 (A8), U3.T8 (A8)
SA9: RM19.2.2 (2), U2.R3 (A9), U3.R3 (A9)
SA10: RM21.3.2 (2), U2.L7 (A10/AP), U3.L7 (A10/AP)
SA11: RM17.3.2 (2), U2.R7 (A11), U3.R7 (A11)
SA12: RM19.1.2 (2), U2.N7 (A12/#BC), U3.N7 (A12/#BC)
SA13: RM16.1.2 (2), U2.T3 (A13), U3.T3 (A13)
SA14: RM19.3.2 (2), U2.T7 (NC/A14), U3.T7 (NC/A14)
SA15: RM16.4.2 (2), U2.M7 (NC), U3.M7 (NC)
SATA-RXM: C142.1, U1.U20 (RXM_SATA)
SATA-RXP: C143.1, U1.U21 (RXP_SATA)
SATA-TXM: C141.1, U1.T21 (TXM_SATA)
SATA-TXP: C140.1, U1.T20 (TXP_SATA)
SCK: R118.2, U1.V1 (SCK)
SCK#: R119.2, U1.V2 (SCK#)
SCKE0: RM20.3.1 (1), U1.N3 (SCKE0)
SCKE1: SCKE1.1, U1.J4 (SCKE1)
SCS0: RM17.1.2 (2), U2.L2 (#CS), U3.L2 (#CS)
SD0-CLK: SD/MMC1.5 (CLK/SCLK), U1.L20 (SDC0_CLK/UART0_TX/PF2)
SD0-CMD: R30.1, SD/MMC1.3 (CMD/DI), U1.L19 (SDC0_CMD/JTAG_DO1/PF3)
SD0-D0: RM14.2.2 (2), SD/MMC1.7 (DAT0/DO), U1.M19 (SDC0_D0/JTAG_DI1/PF1)
SD0-D1: RM14.3.2 (2), SD/MMC1.8 (DAT1/RES), U1.M20 (SDC0_D1/JTAG_MS1/PF0)
SD0-D2: RM14.1.2 (2), SD/MMC1.1 (DAT2/RES), U1.K19 (SDC0_D2/JTAG_CK1/PF5)
SD0-D3: R29.1, SD/MMC1.2 (CD/DAT3/CS), U1.K20 (SDC0_D3/UART0_RX/PF4)
SD0-DET#: RM14.4.2 (2), SD/MMC1.9 (CP_E), U1.B6 (LCD1_D1/ATAA1/UART3_RX/EINT1/CSI1_D1/PH1)
SDBG0: U1.P8 (SDBG0)
SDBG1: U1.R8 (SDBG1)
SDC3-CLK: SD/MMC2.5 (CLK/SCLK), U1.B18 (SDC3_CLK/PI5)
SDC3-CMD: R10.1, SD/MMC2.2 (CMD/DI), U1.A18 (SDC3_CMD/PI4)
SDC3-D0: RM15.2.1 (1), SD/MMC2.7 (DAT0/DO), U1.A17 (SDC3_D0/PI6)
SDC3-D1: RM15.1.1 (1), SD/MMC2.8 (DAT1/RES), U1.B17 (SDC3_D1/PI7)
SDC3-D2: RM15.3.1 (1), SD/MMC2.9 (DAT2/RES), U1.A16 (SDC3_D2/PI8)
SDC3-D3: R11.1, SD/MMC2.1 (CD/DAT3/CS), U1.B16 (SDC3_D3/PI9)
SDQ0: RM1.2.2 (2), U1.AB4 (SDQ0)
SDQ1: RM2.2.2 (2), U1.AC7 (SDQ1)
SDQ2: RM1.3.2 (2), U1.AC4 (SDQ2)
SDQ3: RM2.3.2 (2), U1.AB8 (SDQ3)
SDQ4: RM2.4.2 (2), U1.AC8 (SDQ4)
SDQ5: RM1.4.2 (2), U1.AB5 (SDQ5)
SDQ6: RM2.1.2 (2), U1.AB7 (SDQ6)
SDQ7: RM1.1.2 (2), U1.AC3 (SDQ7)
SDQ8: RM3.2.2 (2), U1.AB2 (SDQ8)
SDQ9: RM4.2.2 (2), U1.Y1 (SDQ9)
SDQ10: RM3.3.2 (2), U1.AC2 (SDQ10)
SDQ11: RM4.3.2 (2), U1.Y2 (SDQ11)
SDQ12: RM4.4.2 (2), U1.AA1 (SDQ12)
SDQ13: RM3.4.2 (2), U1.AB3 (SDQ13)
SDQ14: RM4.1.2 (2), U1.W2 (SDQ14)
SDQ15: RM3.1.2 (2), U1.AC1 (SDQ15)
SDQ16: RM5.2.2 (2), U1.N1 (SDQ16)
SDQ17: RM6.2.2 (2), U1.T2 (SDQ17)
SDQ18: RM5.3.2 (2), U1.N2 (SDQ18)
SDQ19: RM6.3.2 (2), U1.U1 (SDQ19)
SDQ20: RM6.4.2 (2), U1.U2 (SDQ20)
SDQ21: RM5.4.2 (2), U1.P1 (SDQ21)
SDQ22: RM6.1.2 (2), U1.T1 (SDQ22)
SDQ23: RM5.1.2 (2), U1.M2 (SDQ23)
SDQ24: RM7.2.2 (2), U1.L1 (SDQ24)
SDQ25: RM8.2.2 (2), U1.H1 (SDQ25)
SDQ26: RM7.3.2 (2), U1.L2 (SDQ26)
SDQ27: RM8.3.2 (2), U1.H2 (SDQ27)
SDQ28: RM8.4.2 (2), U1.J1 (SDQ28)
SDQ29: RM7.4.2 (2), U1.M1 (SDQ29)
SDQ30: RM8.1.2 (2), U1.G2 (SDQ30)
SDQ31: RM7.1.2 (2), U1.K2 (SDQ31)
SDQM0: R110.1, U2.E7 (DML)
SDQM1: R111.1, U2.D3 (DMU)
SDQM2: R112.1, U3.E7 (DML)
SDQM3: R113.1, U3.D3 (DMU)
SDQS0: R106.1, U2.F3 (DQSL)
SDQS0_N: R107.1, U2.G3 (#DQSL)
SDQS1: R108.1, U2.C7 (DQSU)
SDQS1_N: R109.1, U2.B7 (#DQSU)
SDQS2: R114.1, U3.F3 (DQSL)
SDQS2_N: R115.1, U3.G3 (#DQSL)
SDQS3: R116.1, U3.C7 (DQSU)
SDQS3_N: R117.1, U3.B7 (#DQSU)
SD_VCC: C103.2, C104.2, L4.2, SD/MMC1.4 (VDD)
SD_VCC1: C56.2, C115.2, L5.2, SD/MMC2.4 (VDD)
SEARCH_BUT: GPIO-1.12, R99.2, R100.1, SEARCH233.1_1 (1)
SPI1-CLK: U1.E16 (EINT29/SPI1_CLK/UART2_CTS/PI17), UEXT2.9
SPI1-CS0: R84.1, U1.E17 (EINT28/SPI1_CS0/UART2_RTS/PI16), UEXT2.10
SPI1-MISO: U1.D14 (EINT31/SPI1_MISO/UART2_RX/PI19), UEXT2.7
SPI1-MOSI: U1.E15 (EINT30/SPI1_MOSI/UART2_TX/PI18), UEXT2.8
SPI2-CLK: U1.K21 (NCE5/SPI2_CLK/PC20), UEXT1.9
SPI2-CS0: R95.1, U1.L21 (NCE4/SPI2_CS0/PC19), UEXT1.10
SPI2-MISO: U1.J20 (NCE7/SPI2_MISO/PC22), UEXT1.7
SPI2-MOSI: U1.J21 (NCE6/SPI2_MOSI/PC21), UEXT1.8
SRST: R12.2, U1.AA6 (SRST)
TPX1: C127.2, LCD_CON233.37, U1.Y22 (XP_TP)
TPX2: C129.2, LCD_CON233.38, U1.AA22 (XN_TP)
TPY1: C131.2, LCD_CON233.39, U1.Y23 (YP_TP)
TPY2: C132.2, LCD_CON233.40, U1.AA23 (YN_TP)
TSD_CLK: R127.2, U8.40 (NC)
TSD_CMD: R128.2, U8.33 (NC)
TSD_D0: R122.2, U8.47 (NC)
TSD_D1: R123.2, U8.46 (NC)
TSD_D2: R124.2, R125.2, U8.45 (NC)
TSD_D3: R126.2, U8.27 (NC)
TVIN0: C181.2, GPIO-1.22, U1.AC18 (TVIN0)
TVIN1: C183.2, GPIO-1.24, U1.AB18 (TVIN1)
TVIN2: C185.2, GPIO-1.26, U1.AA17 (TVIN2)
TVIN3: C188.2, GPIO-1.28, U1.Y17 (TVIN3)
TVOUT3: GPIO-1.20, U1.AB17 (TVOUT3)
TWI0-SCK: GPIO-2.5, R75.1, U1.A15 (TWI0_SCK/PB0), U12.2 (SCK)
TWI0-SDA: GPIO-2.7, R76.1, U1.B15 (TWI0_SDA/PB1), U12.1 (SDA)
TWI1-SCK: R13.2, R82.1, U1.A8 (TWI1_SCK/PB18), U6.6 (SCL), UEXT2.5
TWI1-SDA: R14.1, R83.1, U1.B8 (TWI1_SDA/PB19), U6.5 (SDA), UEXT2.6
TWI2-SCK: R93.1, U1.C8 (TWI2_SCK/PB20), UEXT1.5
TWI2-SDA: R94.1, U1.C7 (TWI2_SDA/PB21), UEXT1.6
UART0-RX: D3.A, GPIO-2.34, R105.1, U1.B7 (UART0_RX/IR1_RX/PB23)
UART0-TX: GPIO-2.36, U1.A7 (UART0_TX/IR1_TX/PB22), UART0.2
UART6-RX: U1.D16 (SPI0_MISO/UART6_RX/EINT25/PI13), UEXT1.4
UART6-TX: U1.C16 (SPI0_MOSI/UART6_TX/EINT24/PI12), UEXT1.3
UART7-RX: U1.E13 (HSDA/UART7_RX/PS2_SDA0/PI21), UEXT2.4
UART7-TX: U1.E14 (HSCL/UART7_TX/PS2_SCK0/PI20), UEXT2.3
UBOOT_SEL: RECOVERY233.2_1 (0), U1.W8 (UBOOT_SEL)
UDM0: U1.N20 (DM0), USB_OTG233.D-
UDM1: U1.P20 (DM1), USB_HOST233.1.2
UDM2: U1.R20 (DM2), USB_HOST233.2.2
UDP0: U1.N21 (DP0), USB_OTG233.D+
UDP1: U1.P21 (DP1), USB_HOST233.1.3
UDP2: U1.R21 (DP2), USB_HOST233.2.3
USB0-DRV: R44.2, U1.C12 (I2S_DO1/PB9), U9.4 (EN), U12.6 (N_VBUSEN)
USB0-IDDET: R52.2, U1.B5 (LCD1_D4/ATAD0/UART4_TX/EINT4/CSI1_D4/PH4), USB_OTG233.ID
USB0-VBUSDET: C122.1, R42.1, R46.2, U1.C5 (LCD1_D5/ATAD1/UART4_RX/EINT5/CSI1_D5/PH5)
USB1-DRV: R47.2, U1.A4 (LCD1_D6/ATAD2/UART5_TX/MS_BS/EINT6/CSI1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), U10.4 (EN)
USB2-DRV: R54.2, U1.A5 (LCD1_D3/ATAIRQ/UART3_CTS/EINT3/CSI1_D3/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), U11.4 (EN)
V+: 1.5V233.1, C1.1, C2.2, C3.2, C4.2, C5.2, C6.2, C7.2, C8.2, C9.2, C10.2, C11.2, C17.1, C28.2, C29.2, C30.2, C31.2, C32.2, C33.2, C34.2, C36.2, C37.2, C38.2, C39.2, C40.2, C41.2, C42.2, C43.2, C44.2, C45.2, C46.2, C47.2, C48.2, C49.2, C50.2, C51.2, C52.2, C53.2, C54.2, C55.2, C195.1, C198.1, C199.1, C224.2, C225.2, C226.2, C227.2, C228.2, C229.2, C230.2, C231.2, C232.2, L18.2, R1.2, R4.2, R6.2, R77.1, U1.G5 (VCC_DRAM), U1.H5 (VCC_DRAM), U1.L5 (VCC_DRAM), U1.M5 (VCC_DRAM), U1.R5 (VCC_DRAM), U1.T5 (VCC_DRAM), U1.W5 (VCC_DRAM), U1.W6 (VCC_DRAM), U1.W7 (VCC_DRAM), U1.Y6 (VCC_DRAM), U2.A1 (VDDQ), U2.A8 (VDDQ), U2.B2 (VDD), U2.C1 (VDDQ), U2.C9 (VDDQ), U2.D2 (VDDQ), U2.D9 (VDD), U2.E9 (VDDQ), U2.F1 (VDDQ), U2.G7 (VDD), U2.H2 (VDDQ), U2.H9 (VDDQ), U2.K2 (VDD), U2.K8 (VDD), U2.N1 (VDD), U2.N9 (VDD), U2.R1 (VDD), U2.R9 (VDD), U3.A1 (VDDQ), U3.A8 (VDDQ), U3.B2 (VDD), U3.C1 (VDDQ), U3.C9 (VDDQ), U3.D2 (VDDQ), U3.D9 (VDD), U3.E9 (VDDQ), U3.F1 (VDDQ), U3.G7 (VDD), U3.H2 (VDDQ), U3.H9 (VDDQ), U3.K2 (VDD), U3.K8 (VDD), U3.N1 (VDD), U3.N9 (VDD), U3.R1 (VDD), U3.R9 (VDD)
VCC: 3.3V233.1, C68.2, C69.2, C70.2, C77.2, C78.2, C79.2, C80.2, C81.2, C82.2, C83.2, C84.2, C85.2, C89.2, C90.2, C117.2, C118.2, C119.2, C208.1, C211.1, C212.1, C219.1, D1.A, GPIO-1.3, GPIO-2.3, GPIO-3.3, L1.2, L2.2, L4.1, L5.1, L21.2, LAN233.AG, LCD_CON233.3, R10.2, R11.2, R13.1, R14.2, R18.1, R19.1, R21.1, R28.2, R29.2, R30.2, R31.2, R51.2, R52.1, R60.1, R72.1, R74.1, R75.2, R76.2, R82.2, R83.2, R84.2, R89.1, R93.2, R94.2, R95.2, R105.2, R121.1, R125.1, R130.1, RM9.1.1 (1), RM10.1.2 (2), RM10.2.2 (2), RM14.1.1 (1), RM14.2.1 (1), RM14.3.1 (1), RM14.4.1 (1), RM15.1.2 (2), RM15.2.2 (2), RM15.3.2 (2), RM15.4.2 (2), RM25.1.2 (2), RM25.2.2 (2), RM25.3.2 (2), U1.AB19 (HPVCCIN), U1.H8 (VCC), U1.H9 (VCC), U1.H10 (VCC), U1.H15 (VCC), U1.H19 (VCC_NAND), U1.J8 (VCC), U1.J9 (VCC), U1.J10 (VCC), U1.J14 (VCC), U1.J19 (VCC_NAND), U1.N19 (VCC_CARD), U1.W12 (VCC_LVDS), U1.W13 (VCC_LVDS), U1.W14 (VCC_LVDS), U6.8 (VCC), U7.37 (ANE), U7.38 (DUPLEX), U7.39 (SPEED), U7.41 (LDPS), U7.44 (MII/SNIB), U8.1 (NC), U8.12 (VCC), U8.24 (NC), U8.34 (NC), U8.37 (VCC), U8.39 (NC), UART0.1, UEXT1.1, UEXT2.1, VPS+233.1, VR1.1 (VIN), VR1.3 (CE)
VCC/2: 1.2V_CPU233.1, C57.2, C58.2, C59.2, C60.2, C61.2, C62.2, C159.1, C160.1, L13.2, U1.H11 (VDD_CPU), U1.H12 (VDD_CPU), U1.H13 (VDD_CPU), U1.H14 (VDD_CPU), U1.J12 (VDD_CPU), U1.J13 (VDD_CPU), U12.10 (DCDC2)
VCCINT: 1.2V_INT233.1, C18.2, C19.2, C20.2, C21.2, C22.2, C23.2, C24.2, C25.2, C26.2, C27.2, C164.1, C165.1, L14.2, R3.2, R53.2, R68.2, U1.J15 (VDD_INT), U1.J16 (VDD_INT), U1.K9 (VDD_INT), U1.K10 (VDD_INT), U1.K15 (VDD_INT), U1.L8 (VDD_INT), U1.L9 (VDD_INT), U1.R9 (VDD_INT), U1.R10 (VDD_INT), U1.T8 (VDD_INT), U12.17 (DCDC3)
VDD: 2.5V233.1, C220.1, C221.1, R23.2, R66.2, R71.1, VR1.5 (VOUT)
VDD_RTC: C101.2, C102.2, C172.1, U1.K8 (RTC_VDD), U12.28 (LDO1)
VGA-B: GPIO-1.35, RM24.3.2 (2), U1.AB16 (TVOUT1), VGA233.2
VGA-G: GPIO-1.33, RM24.4.2 (2), U1.AC16 (TVOUT0), VGA233.3
VGA-R: GPIO-1.37, RM24.2.2 (2), U1.AC17 (TVOUT2), VGA233.1
VGA_HSYNC: FET3.3 (D), GPIO-1.29, R104.2, VGA233.5
VGA_VSYNC: FET2.3 (D), GPIO-1.31, R41.2, VGA233.4
VINT: C167.2, U12.26 (VINT)
VMIC: C148.2, R57.2, U1.AA21 (VMIC)
VOL+_BUT: GPIO-1.6, R96.2, R97.1, VOL+233.1_1 (1)
VOL-_BUT: GPIO-1.8, R97.2, R98.1, VOL-233.1_1 (1)
VPP: 3.0VA233.1, C109.2, R69.1 (1.1), R91.1, U1.T19 (AVCC), U13.1 (EN)
WEN: RM18.1.2 (2), U2.L3 (#WE), U3.L3 (#WE)
XTALI: C99.2, Q3.2, U1.N23 (CLK24M_IN)
XTALI1: C72.2, Q1.2, U7.46 (X1)
XTALO: C100.2, Q3.1, U1.N22 (CLK24M_OUT)
XTALO1: C73.2, Q1.1, U7.47 (X2)

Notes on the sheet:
POWER SUPPLY CIRCUIT
LI-ION_BATTERY
2 x [2Gb DDR3 SDRAM (256Mx8)]
MicroSD
UEXTs
6-16VDC
0.19V
0.39V
0.60V
0.80V
0.98V
Buttons
USB-OTG
Iset = 6800/Rs
Iset = 523mA
USB-HOSTs
3V3/30mA
3V/200mA
2V8/200mA
1V2/1.2A
1V2/1.6A
HSYNC
VSYNC
3.3V
GND
5.0V
CLK
PWRE
BKL
L/R
U/D
NAND Flash
32Gb (4096M x 8bit)
GPIO EXTENSION
LCD EXTENSION
Must be Floating!!!
Ethernet
EEPROM
MAC Address
16 Kbit

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
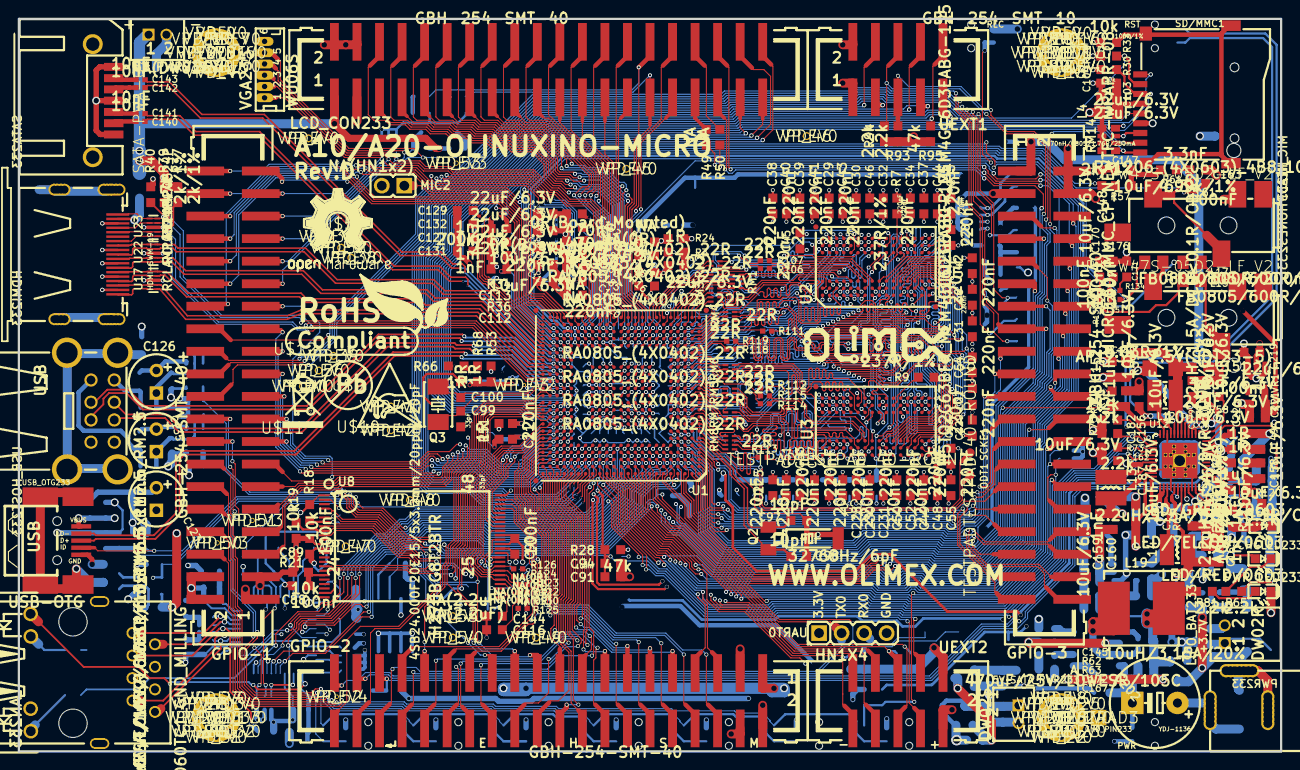
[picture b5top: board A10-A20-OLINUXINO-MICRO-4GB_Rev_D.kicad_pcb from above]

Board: 4 copper layers, 142.2 x 82.6 mm, 558 parts (0 on the bottom side), 539 nets.

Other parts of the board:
U$5: LOGO-OPENHARDWARE_8X8
U$6, U$8: OLIMEX1_V
U$9: PB
U$10: ESD_SYMBOL
U$11: RECYCLE_BIN1%2f8
U$12: ROHS
